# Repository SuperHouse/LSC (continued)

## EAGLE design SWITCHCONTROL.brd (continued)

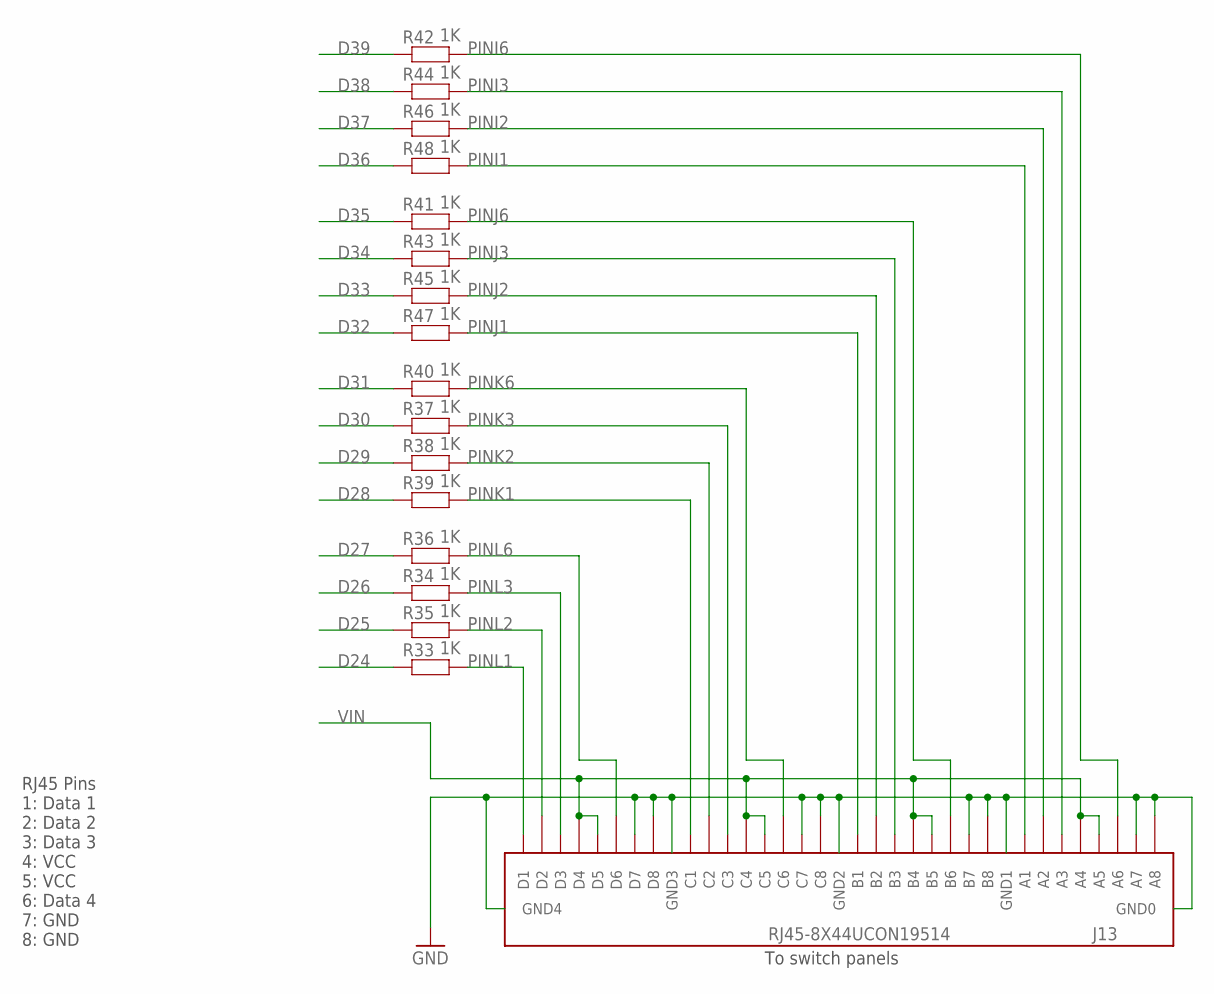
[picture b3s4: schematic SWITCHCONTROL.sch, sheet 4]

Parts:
J13: RJ45-8X44UCON19514; RJ45-8X4
R33, R34, R35, R36, R37, R38, R39, R40, R41, R42, R43, R44, R45, R46, R47, R48: 1K; 0603

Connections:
D24: R33.1; also elsewhere on the board
D25: R35.1; also elsewhere on the board
D26: R34.1; also elsewhere on the board
D27: R36.1; also elsewhere on the board
D28: R39.1; also elsewhere on the board
D29: R38.1; also elsewhere on the board
D30: R37.1; also elsewhere on the board
D31: R40.1; also elsewhere on the board
D32: R47.1; also elsewhere on the board
D33: R45.1; also elsewhere on the board
D34: R43.1; also elsewhere on the board
D35: R41.1; also elsewhere on the board
D36: R48.1; also elsewhere on the board
D37: R46.1; also elsewhere on the board
D38: R44.1; also elsewhere on the board
D39: R42.1; also elsewhere on the board
GND: J13.A7, J13.A8, J13.B7, J13.B8, J13.C7, J13.C8, J13.D7, J13.D8, J13.GND0, J13.GND1, J13.GND2, J13.GND3, J13.GND4; also elsewhere on the board
PINI1: J13.A1, R48.2
PINI2: J13.A2, R46.2
PINI3: J13.A3, R44.2
PINI6: J13.A6, R42.2
PINJ1: J13.B1, R47.2
PINJ2: J13.B2, R45.2
PINJ3: J13.B3, R43.2
PINJ6: J13.B6, R41.2
PINK1: J13.C1, R39.2
PINK2: J13.C2, R38.2
PINK3: J13.C3, R37.2
PINK6: J13.C6, R40.2
PINL1: J13.D1, R33.2
PINL2: J13.D2, R35.2
PINL3: J13.D3, R34.2
PINL6: J13.D6, R36.2
VIN: J13.A4, J13.A5, J13.B4, J13.B5, J13.C4, J13.C5, J13.D4, J13.D5; also elsewhere on the board

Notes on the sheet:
To switch panels
RJ45 Pins 1: Data 1 2: Data 2 3: Data 3 4: VCC 5: VCC 6: Data 4 7: GND 8: GND

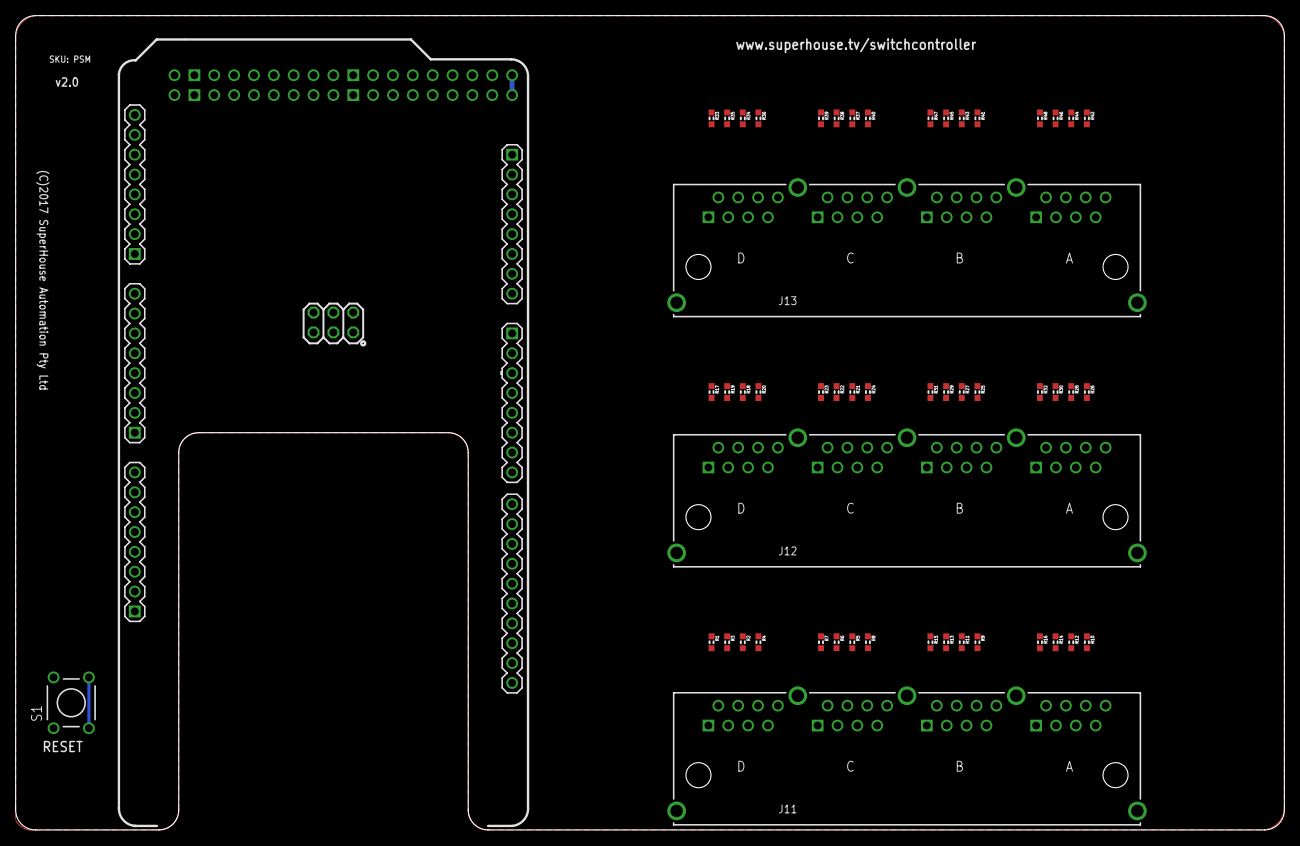
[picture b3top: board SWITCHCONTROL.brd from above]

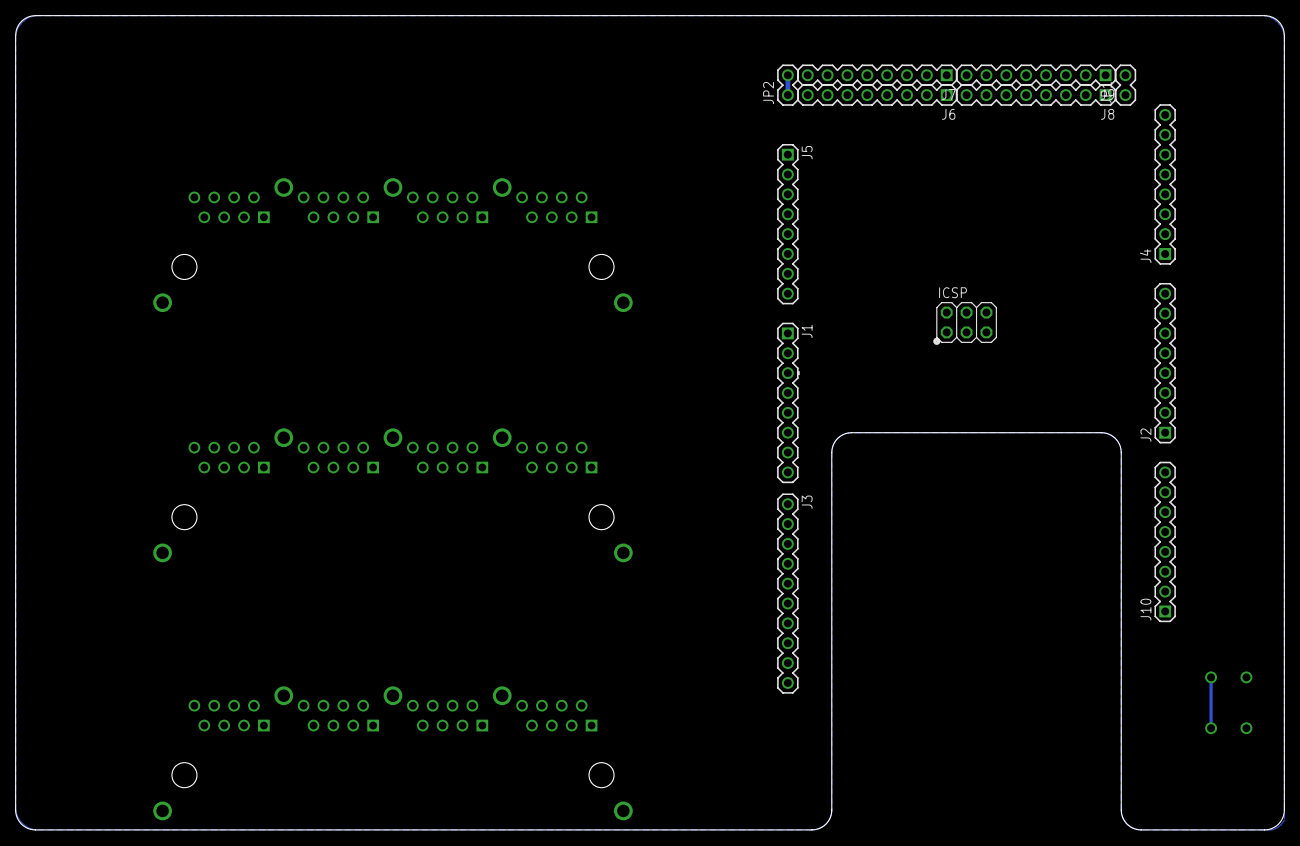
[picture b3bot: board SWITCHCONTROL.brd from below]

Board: 2 copper layers, 162.3 x 104.1 mm, 65 parts (13 on the bottom side), 100 nets.

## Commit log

2018-03-28 Initial import of unfinished project
2019-04-24 Renamed project files
2019-07-30 Schematic and routing
2019-09-02 Fixed README
2019-09-04 Added DC power jack and screw terminal
2019-09-04 Renamed project files to match SKU
2019-09-07 Routing and silkscreen for Ethernet pass-through and external power
2019-09-07 Board and schematic labelling
2019-09-07 Added fiducials and optimised GND pathways
2019-09-13 Final routing, plus ERC and DRC for v1.0 release
2019-09-13 Minor silkscreen tweak
2020-04-08 Converted to I2C-BREAKOUT header for v2.0 release
2020-04-30 Moved holes back from edge for v2.1 release
2020-04-30 Added top layer SMT mount file
2021-03-11 Added PDF of schematic.
2021-04-12 Removed Ethernet passthrough and shortened board.
2021-04-12 Removed outdated SMT mount file.
2021-04-12 Removed outdated schematic PDF.
2021-04-12 Moved hardware files into subdirectory.
2021-04-12 Updated README to match shortened board.
2021-04-13 Renumbered parts to optimise production.
2021-04-13 Added render of PCB.
2021-04-13 Embedded render of PCB.
2021-04-15 Major clean-up in preparation for recreating x8 and x16 versions based on the x24 version. Moved rear silkscreen into left third. Increased size of all data traces. Improved bottom power plane pour. 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
2021-04-15 Added weak pull-up on RESET line.
2021-04-15 Bumped version to v3.0 for release.
2021-04-15 Major rework for v3.0 release of all versions.
2021-04-15 Added v3.0 render.
2021-04-15 Added render and links to other versions to README.
2021-04-15 Added .gitignore.
2021-04-15 Added link to 24-port version with passthrough.
2021-04-22 Consolidated files from 24-port passthrough version into LSC project.
2021-04-22 Consolidated files from 8-port version into LSC project.
2021-04-22 Consolidated files from 16-port version into LSC project.
2021-04-22 Consolidated images from 8-port version into LSC project.
2021-04-22 Consolidated images from 16-port version into LSC project.
2021-04-22 Consolidated images from 24-port passthrough version into LSC project.
2021-04-22 Began replacement of discrete resistors with resistor arrays.
2021-04-22 Updated README as part of merging 8, 16, and 24 port versions.
2021-04-22 Merged in firmware for EtherTen / EtherMega.
2021-04-24 initial changes to get working locally added support for watchdog changed button numbering to 0-based (i.e. 0-95) added support for custom MQTT base topic
2021-04-24 ignore config.h
2021-04-24 updates after PR review
2021-04-25 don't attempt to reconnect on every loop, pause for 5s
2021-04-25 add option in config to set mqtt port
2021-04-25 implement mcp detection
2021-04-25 Progress on converting resistors to arrays and adding pullups.
2021-04-25 Added Ben Jones to contributor list.
2021-04-25 Moved string into flash memory and applied automatic Arduino formatting.
2021-04-25 Use forked SH1106 library to drive I2C OLED display.
2021-04-25 Added image of assembled prototype.
2021-04-25 OLED defaults to enabled in example config.
2021-04-26 add incrementing backoff when reconnecting to MQTT
2021-04-26 store button state for each chip in a single byte
2021-04-26 improve i2c scanner to detect presence of oled and gaps in mcp23017 addresses
2021-04-26 normalise variable names code formatting
2021-05-03 add support for different button event types
2021-05-06 scan for oled + button mcp display startup message
2021-05-06 add button event display
2021-05-17 moin's changes to show port animations
2021-05-20 add usm firmware for handling button/switch/contact inputs (#4)
2021-05-20 tidy up config.h.example
2021-05-21 added some docs reduce max mqtt reconnect backoff time to 5s reduced size of event payload
2021-05-21 low memory warning if use dhcp for ip address - reduce max MCP count to conserve memory
2021-05-21 add better handling for ignored MCPs during I2C scan
2021-05-21 add support for TOGGLE switches (#5)
2021-05-22 rename MCP_COUNT -> MAX_MCP_COUNT
2021-05-23 more ram to save (#6)
    save ram by avoiding "static" where possible
2021-05-23 working but memory issues on uno
2021-05-24 Added configurable invert logic
2021-05-27 OLED integration (#9)
    * more ram to save
    save ram by avoiding "static" where possible
    * Integration of OLED support
    integrated OLED support with port animation and event display at buttom line. OLED will be dimmed after some time of inactivity (parameter in config.h). Renamed everyting to USM and event.
    * some minor updates
    show MAC addess on OLED
2021-05-30 remove ENABLE_OLED config variable - rely on I2C scanner minor code formatting
2021-05-30 add support for rotary encoder inputs (#10)
2021-05-31 fix up toggle handling (broke after rotary addition)
2021-05-31 increase mqtt message buffer (to allow for 8xMCPs/128xinputs)
2021-06-04 Replace discrete resistors with resistor networks. Add hardware pull-ups to all input lines. Routing, ERC, and DRC for v3.0 release.
2021-06-04 Added render of v3.0 24-port board.
2021-06-06 fix a couple of errors when compiling for ESP8266 and ESP32
2021-06-06 implementation of ESP8266 and ESP32 incl, WiFi
    this is tested with AVR: UNO, ESP8266: LOLIN (WEMOS) D1 mini pro, ESP32: AI Thinker ESP32-CAM and 1 MCP and OLED
    There are still TO DO's to improve WiFi / MQTT robustness
2021-06-06 added static IP support and wifi connection checks
2021-06-08 Major rework: rerouted entire board.
2021-06-08 Regenerated 16-port version from updated 24-port version.
2021-06-08 Regenerated 8-port version from updated 16-port version.
2021-06-08 Increased track size on VCC.
2021-06-08 tidy up config var names check for NULL instead of zero length strings
2021-06-08 use mqtt_client_id in topics (so it is configurable)
2021-06-08 set default config to publish events to test.mosquitto.org
2021-06-08 fix a couple of errors when compiling for ESP8266 and ESP32 (#11)
2021-06-08 Config tidyup (#12)
    * tidy up config var names
    check for NULL instead of zero length strings
    * use mqtt_client_id in topics (so it is configurable)
    * set default config to publish events to test.mosquitto.org
2021-06-13 allow usm to run if no network/mqtt (#14)
2021-06-13 updated sketch header with main contributors
2021-06-15 Use MCP h/w polarity function for inverting inputs (#15)
2021-06-18 speed up button client detection by 50ms
2021-06-25 ensure input state is reset when the type is changed (stops problems when changing from ROTARY and the state is in an unknown state for the other types)
2021-07-04 remove usage of min() as not supported on ESP32 (#19)
2021-07-06 merge in moin's changes to improve debouncing (#21)
    * merge in moin's changes to improve debouncing
2021-07-06 increment version to 4.3
2021-07-20 Removed I2C breakouts that are now in their own dedicated repository.
2021-07-20 Fixed formatting of credits.
2021-07-23 Optimisations for faster loop cycles (#23)
    * Optimisations for faster loop cycles
    * Fix bug in state reset on type change
2021-07-26 reverted to using software based invert logic (#25)
2021-07-26 default all inputs to SWITCH (instead of BUTTON) on startup (#26)
2021-07-30 allow mcp23017 internal pullups to be enabled/disabled
2021-07-30 add notes about changes to mcp23017 library in v2+
2021-07-30 Make MCP23017 internal pullups configurable (#27)
    * allow mcp23017 internal pullups to be enabled/disabled
    * add notes about changes to mcp23017 library in v2+
2021-07-30 allow different debounce times for different input types
2021-07-30 added specific debounce times for rotary inputs
2021-07-31 allow different debounce times for different input types (#26)
    * allow different debounce times for different input types
2021-07-31 improve mcp scanning
2021-07-31 improve mcp scanning (#28)
2021-08-01 changed to fixed mcp address list, defined in config.h renamed all user configurable variables to all caps
2021-08-01 increment version to 4.8
2021-08-04 remove firmware (after migration to USM repo) remove ben jones from contributor lists add link to usm repo in readme
2021-08-04 remove firmware (after migration to USM repo) (#30)
    remove ben jones from contributor lists
    add link to usm repo in readme
